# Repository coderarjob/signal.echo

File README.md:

<p align="center">
    
    <br/>
    <br/>

</p>

## About

This is a hardware project based on Atmega8A microcontroller. This project came about from a
personal need for a demo board to test my new oscilloscope. I plan to create a complete PCB
along with firmware in this repo.

**Caution**: The `master` branch contains changes for the upcoming version and may not always be
stable. If you wish to manufacture, use the latest `release/version_x.x` branch or one of the
[released](https://github.com/coderarjob/signal.echo/releases) versions.

See [LICENCE](./LICENSE) for terms under which this project is released and developed.

### Screenshots

##### 1. Serial RS232 (TTL Level) decoding test

##### 2. Serial I2C decoding test

##### 3. Positive & negative Runt detection pulse

##### 4. Burst pulses (long delay)

##### 5. Two burst (time coorolated) pulses

##### 6. Sine wave

##### 7. Amplitude Modulation wave

##### 8. Triangle wave

##### 9. Sawtooth wave

### Goals

- [X] Firmware: RS232 sample output (positive)
- [X] Firmware: I2C sample output
- [X] Firmware: Runt pulse (+ve & -ve runt pulses)
- [X] Firmware: Sine wave pattern
- [X] Firmware: Amplitude Modulation wave pattern
- [X] Firmware: Triangle wave pattern
- [X] Firmware: Sawtooth wave pattern
- [X] Firmware: Burst data in two lines
- [X] Firmware: Separate arch independent codes
- [X] Unittests: Add unittests for utils
- [X] Unittests: Add unittests for existing tests
- [X] Manufacturing: Build the PCB board

## Building prerequisites

1. Requires Linux environment for building.
2. GNU Make
3. avr-gcc
4. avr-libc

### Firmware

Build the firmware using the following command. Firmware binary is the `./out/firmware.hex` file.

```bash
BUILD_DIR=out make
```

To program using avrdude we run the following command.

```bash
make program
```

When programming a new microcontroller, we also need to program the required fuse bits. This can be
using the following command

```bash
make program_fuses
```

### Unittests

We can build every unittests and run them using the `run` target.

```bash
BUILD=ut BUILD_DIR=out/ut make run
```

### Tools

Some tools which are used exclusively in this project are/will be put into the `tools` folder. Each
may have different prerequisites and build procedures. For information see `Readme.md` of each
tool.

# Feedback

Open a GitHub issue or drop a email at arjobmukherjee@gmail.com. I would love to hear your
suggestions and feedbacks.

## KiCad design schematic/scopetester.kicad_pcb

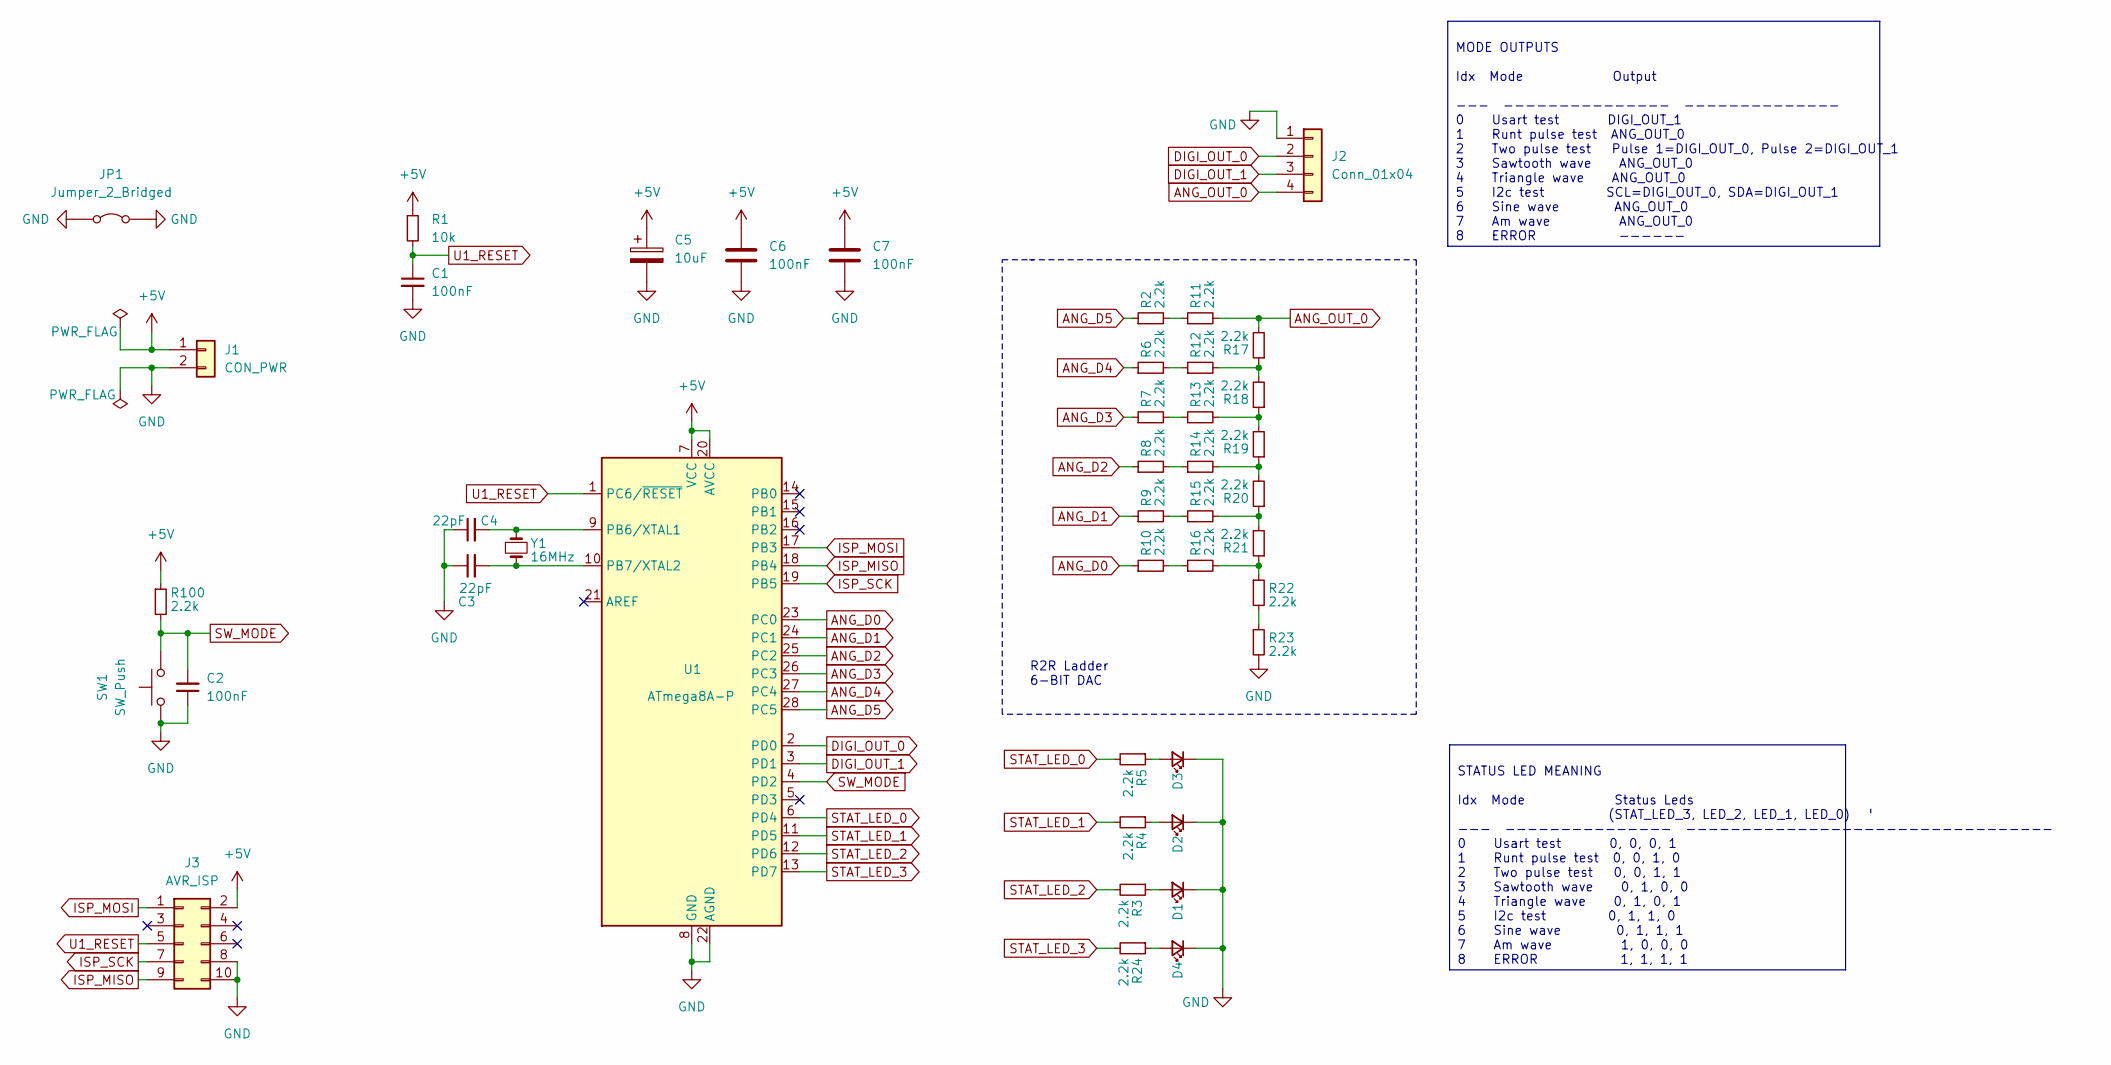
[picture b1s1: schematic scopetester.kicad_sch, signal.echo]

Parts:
C1, C2, C6, C7: 100nF; C_Disc_D3.0mm_W1.6mm_P2.50mm
C3, C4: 22pF; C_Disc_D3.0mm_W1.6mm_P2.50mm
C5: 10uF; CP_Radial_D5.0mm_P2.50mm
D1, D2, D3, D4: LED_Small; LED_D3.0mm
J1: CON_PWR; PinHeader_1x02_P2.54mm_Vertical
J2: Conn_01x04; PinHeader_1x04_P2.54mm_Vertical
J3: AVR_ISP; PinHeader_2x05_P2.54mm_Vertical
JP1: Jumper_2_Bridged; R_Axial_DIN0207_L6.3mm_D2.5mm_P7.62mm_Horizontal
R1: 10k; R_Axial_DIN0207_L6.3mm_D2.5mm_P7.62mm_Horizontal
R2, R3, R4, R5, R6, R7, R8, R9, R10, R11, R12, R13, R14, R15, R16, R17, R18, R19, R20, R21, R22, R23, R24: 2.2k; R_Axial_DIN0207_L6.3mm_D2.5mm_P7.62mm_Horizontal
R100: 2.2k; R_Axial_DIN0411_L9.9mm_D3.6mm_P5.08mm_Vertical
SW1: SW_Push; SW_PUSH_6mm_H4.3mm
U1: ATmega8A-P; DIP-28_W7.62mm
Y1: 16MHz; Crystal_HC49-4H_Vertical

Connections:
+5V: C5.1, C6.1, C7.1, J1.1, J3.2, R1.1, R100.1, U1.7 (VCC), U1.20 (AVCC)
ANG_D0: R10.1, U1.23 (PC0)
ANG_D1: R9.1, U1.24 (PC1)
ANG_D2: R8.1, U1.25 (PC2)
ANG_D3: R7.1, U1.26 (PC3)
ANG_D4: R6.1, U1.27 (PC4)
ANG_D5: R2.1, U1.28 (PC5)
ANG_OUT_0: J2.4, R11.2, R17.2
DIGI_OUT_0: J2.2, U1.2 (PD0)
DIGI_OUT_1: J2.3, U1.3 (PD1)
GND: C1.2, C2.1, C3.1, C4.1, C5.2, C6.2, C7.2, D1.1 (K), D2.1 (K), D3.1 (K), D4.1 (K), J1.2, J2.1, J3.8, J3.10, JP1.1 (A), JP1.2 (B), R23.2, SW1.1, U1.8 (GND), U1.22 (AGND)
ISP_MISO: J3.9, U1.18 (PB4)
ISP_MOSI: J3.1, U1.17 (PB3)
ISP_SCK: J3.7, U1.19 (PB5)
unnamed: D1.2 (A), R3.1
unnamed: D2.2 (A), R4.1
unnamed: D3.2 (A), R5.1
unnamed: D4.2 (A), R24.1
unnamed: R10.2, R16.1
unnamed: R2.2, R11.1
unnamed: R6.2, R12.1
unnamed: R12.2, R17.1, R18.2
unnamed: R7.2, R13.1
unnamed: R13.2, R18.1, R19.2
unnamed: R8.2, R14.1
unnamed: R14.2, R19.1, R20.2
unnamed: R9.2, R15.1
unnamed: R15.2, R20.1, R21.2
unnamed: R16.2, R21.1, R22.1
unnamed: R22.2, R23.1
unnamed: C4.2, U1.9 (PB6/XTAL1), Y1.1
unnamed: C3.2, U1.10 (PB7/XTAL2), Y1.2
STAT_LED_0: R5.2, U1.6 (PD4)
STAT_LED_1: R4.2, U1.11 (PD5)
STAT_LED_2: R3.2, U1.12 (PD6)
STAT_LED_3: R24.2, U1.13 (PD7)
SW_MODE: C2.2, R100.2, SW1.2, U1.4 (PD2)
U1_RESET: C1.1, J3.5, R1.2, U1.1 (PC6/~RESET)

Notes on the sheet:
R2R Ladder 6-BIT DAC
MODE OUTPUTS Idx Mode Output --- --------------- -------------- 0 Usart test DIGI_OUT_1 1 Runt pulse test ANG_OUT_0 2 Two pulse test Pulse 1=DIGI_OUT_0, Pulse 2=DIGI_OUT_1 3 Sawtooth wave ANG_OUT_0 4 Triangle wave ANG_OUT_0 5 I2c test SCL=DIGI_OUT_0, SDA=DIGI_OUT_1 6 Sine wave ANG_OUT_0 7 Am wave A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
STATUS LED MEANING Idx Mode Status Leds (STAT_LED_3, LED_2, LED_1, LED_0) --- --------------- --------------------------------- 0 Usart test 0, 0, 0, 1 1 Runt pulse test 0, 0, 1, 0 2 Two pulse test 0, 0, 1, 1 3 Sawtooth wave 0, 1, 0, 0 4 Triangle wave 0, 1, 0, 1 5 I2c test 0, 1, 1, 0 6 Sine wave 0,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

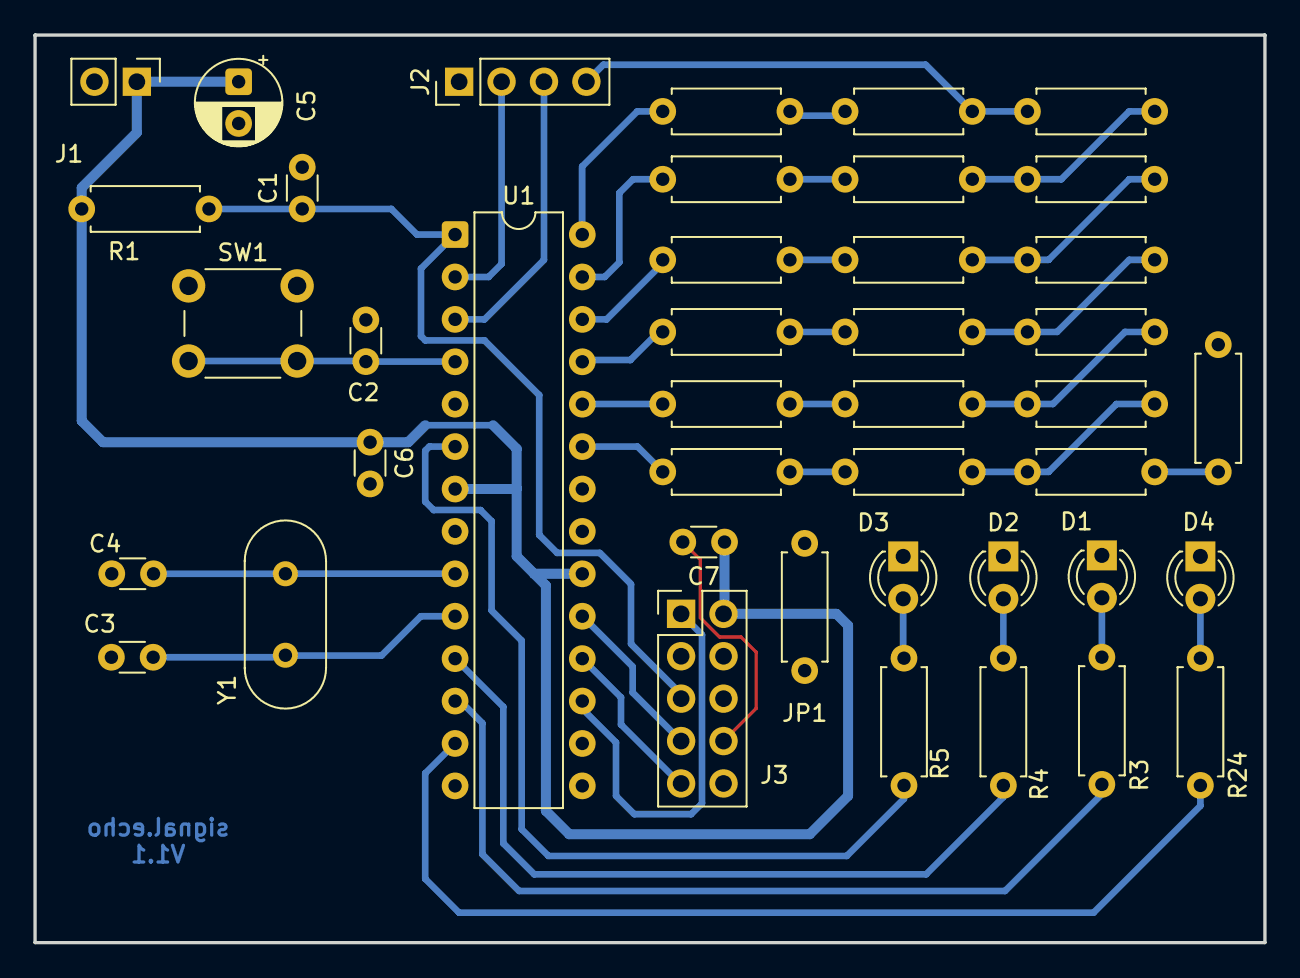
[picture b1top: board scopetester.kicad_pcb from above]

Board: 2 copper layers, 73.7 x 54.4 mm, 42 parts (0 on the bottom side), 38 nets.

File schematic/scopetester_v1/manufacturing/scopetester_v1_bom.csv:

"Id";"Designator";"Footprint";"Quantity";"Designation";"Supplier and ref";
1;"J3";"PinHeader_2x05_P2.54mm_Vertical";1;"AVR_ISP";;;
2;"U1";"DIP-28_W7.62mm";1;"ATmega8A-P";;;
3;"C6,C7,C1,C2";"C_Disc_D3.0mm_W1.6mm_P2.50mm";4;"100nF";;;
4;"JP1";"R_Axial_DIN0207_L6.3mm_D2.5mm_P7.62mm_Horizontal";1;"Jumper_2_Bridged";;;
5;"R8,R5,R9,R23,R12,R21,R18,R3,R6,R19,R16,R20,R7,R11,R14,R13,R15,R24,R4,R22,R2,R10,R17";"R_Axial_DIN0207_L6.3mm_D2.5mm_P7.62mm_Horizontal";23;"2.2k";;;
6;"D1,D3,D4,D2";"LED_D3.0mm";4;"LED_Small";;;
7;"Y1";"Crystal_HC49-4H_Vertical";1;"16MHz";;;
8;"SW1";"SW_PUSH_6mm_H4.3mm";1;"SW_Push";;;
9;"J2";"PinHeader_1x04_P2.54mm_Vertical";1;"Conn_01x04";;;
10;"C5";"CP_Radial_D5.0mm_P2.50mm";1;"1uF";;;
11;"R1";"R_Axial_DIN0207_L6.3mm_D2.5mm_P7.62mm_Horizontal";1;"10k";;;
12;"C4,C3";"C_Disc_D3.0mm_W1.6mm_P2.50mm";2;"22pF";;;
13;"J1";"PinHeader_1x02_P2.54mm_Vertical";1;"CON_PWR";;;

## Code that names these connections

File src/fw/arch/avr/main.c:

#include <avr/io.h>
#include <stdint.h>
#include <util/delay_basic.h>
#include <avr/interrupt.h>
#include <stdbool.h>
#include <main.h>

#define SWITCH_PIN_NO PD2
#define SWITCH_PORT   PORTD
#define SWITCH_PIN    PIND
#define SWITCH_DDR    DDRD

#define STATUS_PIN_NO PB1
#define STATUS_PORT   PORTB
#define STATUS_PIN    PINB
#define STATUS_DDR    DDRB

#define RUNT_OUTPUT_PORT   PORTC
#define RUNT_OUTPUT_DDR    DDRC

#define HOLDOFF_OUTPUT_PIN_NO PD1
#define HOLDOFF_OUTPUT_PORT   PORTD
#define HOLDOFF_OUTPUT_DDR    DDRD

typedef enum TestModes {
    UNKNOWN_TEST,
    USART_TEST,
    HOLDOFF_TEST,
    RUNT_PULSE,
    TEST_COUNT
} TestModes;

static volatile TestModes mode;
static volatile bool mode_isDirty;

static void usart_test();
static void holdoff_test();
static void runt_pulse_test();

ISR (INT0_vect)
{
    if (++mode >= TEST_COUNT) {
        mode = USART_TEST;
    }

    mode_isDirty = true;

    BIT_SET (STATUS_PORT, STATUS_PIN_NO);

    // Wait for the pin to be high
    while (!IS_BIT_SET (SWITCH_PIN, SWITCH_PIN_NO))
        ;

    BIT_CLEAR (STATUS_PORT, STATUS_PIN_NO);
}

void setup_io()
{
    // Make the Interrupt 0 pin as the input
    MAKE_PIN_INPUT_PULLUP (SWITCH_DDR, SWITCH_PORT, SWITCH_PIN_NO);

    // Enable interrupt
#if SWITCH_PIN_NO != PD2
    #error "Wrong switch pin set"
#endif

    BIT_CLEAR_MASK (MCUCR, (1 << ISC01 | 1 << ISC00)); // Trigger at Low level
    BIT_SET_MASK (GICR, (1 << INT0));                  // Enable the interrupt

    // Status port
    MAKE_PIN_OUTPUT (STATUS_DDR, STATUS_PIN_NO);
    BIT_CLEAR (STATUS_PORT, STATUS_PIN_NO);

    sei();
}

__attribute__ ((noreturn)) void main (void)
{
    mode         = USART_TEST;
    mode_isDirty = true;

    setup_io();

    while (1) {
        mode_isDirty = false;
        switch (mode) {
        case USART_TEST:
            usart_test();
            break;
        case HOLDOFF_TEST:
            holdoff_test();
            break;
        case RUNT_PULSE:
            runt_pulse_test();
            break;
        default:
            BIT_SET (STATUS_PORT, STATUS_PIN_NO);
            break;
        }
    }
}

static void runt_pulse_test()
{
    RUNT_OUTPUT_DDR = 0xFF; // Make every pin as output
    uint32_t runt_freq = 1000; // 1 rust pulse every 100 normal pulses

    for (; !mode_isDirty;) {
        if (--runt_freq == 0) {
            runt_freq = 1000;
            RUNT_OUTPUT_PORT = (0x7 << 1); // Make PC1:PC4 as high
            _delay_loop_2 (255);
            RUNT_OUTPUT_PORT = (0);
            _delay_loop_2 (255);
        } else {
            RUNT_OUTPUT_PORT = (0xF<<1); // Make PC1:PC4 as high
            _delay_loop_2 (512);
        }
        RUNT_OUTPUT_PORT = 0x0; // Make all pins low
        _delay_loop_2 (512);
    }

    RUNT_OUTPUT_PORT = 0x0; // Make all pins low
}

static void holdoff_test()
{
    MAKE_PIN_OUTPUT (HOLDOFF_OUTPUT_DDR, HOLDOFF_OUTPUT_PIN_NO);

    for (; !mode_isDirty;) {
        for (int i = 0; i < 20; i++) {
            BIT_SET (HOLDOFF_OUTPUT_PORT, HOLDOFF_OUTPUT_PIN_NO);
            _delay_loop_1 (255);
            BIT_CLEAR (HOLDOFF_OUTPUT_PORT, HOLDOFF_OUTPUT_PIN_NO);
            _delay_loop_1 (255);
        }
        _delay_loop_2 (65535);
    }
}

void usart_test()
{
    usart_on();
    for (char c = 'A'; !mode_isDirty; c + 1 > 'Z' ? c = 'A' : c++) {
        _delay_loop_2 (65535);
        usart_send_string ("Arjob");
        usart_send_char (c);
    }
    usart_off();
}

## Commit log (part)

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2025-05-30 Compiler definitions moved to toolchain file
2025-05-30 Added checks to validate various build variables
2025-05-30 Make rules added to program micro using avrdude
2025-06-04 Targets are build in the respective build.mk
    This make more sense and keeps the outer Makefile less polluted with
    details.
2025-06-04 An example unittest and supporting build added
2025-06-04 New 'run' target to build & run all unittests
2025-06-05 Arch dependent parts separated from independent ones
2025-06-05 Added clang-format for the project
2025-06-05 Static inline small HW functions
    This does reduce the size of the output binary a little bit, but this
    change is more of a placeholder of later functions of the same nature.
2025-06-05 Added utils unittest
2025-06-05 Minor renaming & refactoring in utils.h
2025-06-05 Fix: HIGH8 unittest failure
    To find the highest byte (most significant byte) we must know total
    number of bits. Previously 16 bits was assumed, giving a value higher
    than 65535 thus produced wrong result.
    We now have two separate macros for 16 bit and 32 bit words.
2025-06-05 Unittest for various the main features
    Tests added for:
    * usart_test
    * holdoff_test
    * runt_pulse_test
2025-06-05 Fix: Usart sending wrong first character
2025-06-05 Readme update
2025-06-05 Simplification of mode_is_dirty handler
    Also includes:
    * Minor change to usart_test_normal to check if output char is
    incremented per iteration.
2025-06-05 Fix: Firmware Hex file not passed to Programmer
2025-06-05 Now produces both +ve & -ve runt pulses
    Also include:
    * Associated Unittest update
2025-06-05 Updated yukti.h to latest
    Commit: 6ee1a12
2025-06-05 Add command to build/run unittests in Readme
    Other minor changes to Readme.
2025-06-05 reset_all_mocks() to reset all mock functions
2025-06-06 Fix: Wrong height of Negative runt pulse
    DAC pins are PC1-PC4. PC0 is unused. However low level bits was written
    to PC0-PC2 which caused the problem.
2025-06-06 Readme update with screenshots
2025-06-06 Fix: Readme image alignment issues
2025-06-07 Updated yukti.h to latest
    Commit: 5749a16
    Also includes:
    * Changes to feature_test to use new features in Yukti
2025-06-08 New Two Pulses Test for osc trigger testing
2025-06-08 Readme update with project logo
2025-06-08 Cleanup: Remove hw.h file
    It contained function declarations of functions whose implementations
    are arch dependent, but use is arch independent. By convention such
    functions need no be in a special file. Placing them in main.h file
    would serve the purpose.
2025-06-08 New unittest for two_pulses_test
2025-06-09 Remove separate holdoff test
    Burst mode test can be used for holdoff testing.
2025-06-09 Fix: Current Mode is unknwon state at startup
2025-06-09 Resize burst mode screenshot
    Also includes:
    * Remove holdoff test screenshots
2025-06-10 Replace logo.svg with logo.png
    Vector graphics requires all the referenced font to be present in the
    system to look the same. This is not a guarantee.
    Also includes:
    * Some spelling corrections in Readme
2025-06-10 Burst mode pulses are not narrow & more in number
    There is also a difference in width for the two pulses.
2025-06-15 Analog pins changed. Now starts from PC0 not PC1
2025-06-15 Now only output pins are made output in hw_init()
2025-06-15 DAC is now 6 bits wide instead of 4
2025-06-15 DIGITAL_OUTPUT_PIN_NO0 is now PD0 not PD1
    This aligns with schematic and common sense!
2025-06-15 3 LED's now show current mode
2025-06-15 Fix: Switch debouncing
2025-06-17 Minor updates, makes DAC clear & change of title
2025-06-20 AVR HAL Initial commit
2025-06-20 Using HAL to simplify firmware source code (UT failing)
    * HAL is the only arch dependent code. Tests and even HW initialization
    are done in arch/hw schematic independent way.
    * HW has its versions & is defined in include/hw/<ver>/hwspec.h file.
2025-06-21 hwspec.h should only reference arch independent types
    Otherwise it becomes difficult to unittest with a arch independent
    mocked hal.
    Fixed for AVR_HAL_INTERRUPTS_EXT_INTERRUPT0 which was referenced from
    hwspec.h.
2025-06-21 hal.h file is now included by relative path
    This is done to mock hal.h easily from the build script side.
2025-06-21 Update yukti.h to latest
    Commit: 356c003
    FIX: Build error when mocks & tests are placed separately
    Now the header file is structured to make this separation clear. Things
    that only need to for YT_DEFINE_FUNC*, YT_DECLARE_FUNC* & YT_RESET_MOCK
    macros are defined separate from the ones which are test implementation
    related. The later macros, function etc are now under
2025-06-21 Fix: two_pulses_test used wrong mask for output gpio
2025-06-21 Fix: Baud counter calculation fixed in AVR HAL
2025-06-22 Triangle wave generation added
2025-06-22 Remove zero delays for sawtooth & triangle waves
2025-06-22 Update readme with new Screenshots
2025-06-22 Updated screenshots after last commit
2025-06-22 Added few more informative Screenshots of tests
2025-06-23 Refactoring not include nops for unittests builds
2025-06-25 I2C test added
    Bit banging i2c implementation was added. It sends I2C packet with
    address & data bytes.
    Also includes:
    * Screenshot & Readme update
2025-06-26 Modes updated in schematic & initial PCB layout
2025-06-28 Update yukti.h to latest
    Adds support for parameterised testing
    Commit ID: 4cb359b
    Minor change to make test index & number explicit
2025-06-28 Modify utils test to use parameterised testing
2025-06-28 Updated yukti.h to latest
    Fixes build failure after last commit. New YT_ARG_SUB_ARRAY macro.
    Commit ID: 2dbf4aa
    Added a more complex parameterised test example.
2025-06-28 Status LED out derived from current TestMode
    Previously they were 1:1 mapped.
2025-06-28 Make FW main.c testable, unittest added for it
2025-06-29 Fix: YUKTI_TEST_IMPLEMENTATION not working
    This happens if yukti.h is included from from another header - (for
    example from a mock header) before the YUKTI_TEST_IMPLEMENTATION is
    defined in the test source file.
    One solution is to define YUKTI_TEST_IMPLEMENTATION and include yukti.h
    in the first line in test source.
2025-06-29 Moved DAC_* macros to hwspec.h as they are HW spec related
2025-06-29 Rename TestModes items as TEST_MODE_*
2025-07-02 There are now 4 status LEDs instead of 3
2025-07-02 Fix: Sine wave shape
2025-07-02 Update Readme with Sine wave screenshots
2025-07-04 Sine wave data is put on the .data section explicitly
    This produces same assembly expect for one LDI instruction within the
    loop, related to the 'for' loop in sine_test function. This extra
    instruction causes little dip in the output freq, but is otherwise same.
2025-07-04 Added Timer0 interrupt to avr/hal
2025-07-04 Screenshot update
2025-07-05 Replaced Vcc with +5V in schematic
2025-07-06 Fix: More proper footprints instead of guessing
2025-07-08 Multiple fixes to PCB layout (not final)
2025-07-09 More compact PCB layout
2025-07-09 Finalized PCB layout (edition 1)
    The DRC error of 'mission connection between items' was solved using a
    phony track on the front side. This is just to satisfy KiCad because it
    does not seem to understand that jumper is actually bridged.
2025-07-12 SineX on X and Amplitude Modulation waveform added
    Also includes:
    Corresponding changes to unittests
2025-07-17 Now using 16MHz clock instead of 12MHz
    This increases the waveform frequencies by 33.3%.
2025-07-17 Rename macro MPU_ARCH -> ARCH
    This aligns both Makefile variable & C macro names used to identify MMU
    architecture.
2025-07-17 HAL_BAUD_COUNTER now takes CPU freq as input
2025-07-17 hal_impl_panic is fully mocked for unittest
    Also includes:
    * Fixes compiler warning during unittest 'noreturn function returning'.
2025-07-20 Update yukti.h to latest
    Commit ID: 5f57ade
    Example added for YT_MUST_CALL_* expectations
    Also includes:
    * More comments added to tests
2025-07-25 Upgrade yukti.h to latest
    Commit ID: b96caf0
    Updated to get the following changes:
    * Elapsed time for each is test is displayed
    * New simplified test outputs
2025-08-02 Tool to produce values for our DAC
2025-08-02 Provision to not use Zig's LLVM backend
    Setting `LLVM=0` before `make` will use Zig compiler's native backend
    (which is faster) instead of the default LLVM.
2025-08-02 Using .init to initialize GeneralPurposeAllocator
    As per the deprecation note in the source code and examples in the
    zig release notice.
2025-08-08 Fix: Waves not reaching max and zero values
    It was caused by floor operation in transform_waveform function.
2025-08-10 Update kicad Project to Kicad-9
2025-08-12 bulid.zig replaces Makefile
    It is only required to provide the zig compiler the 'root' file, and
    from that it determines what other files it needs to compile. This is
    difficult to do from within a Makefile.
2025-08-12 Linear interpolation added to smooth to a degree
    Also includes:
    * Option added to enable interpolation & set frequency scaling from
    command arguments.
2025-08-12 Added waveforms data
2025-08-12 Make argument parsing more cleaner
2025-08-13 Move wave generation code into a new file
2025-08-13 Removed Sinx/x wave with much larger AM wave data
    Removed because I think a more dense AM wave will be more useful than a
    sine(x)/x wave for testing purposes.
2025-08-13 Fix: Unittest build failure after d8fdfe4
2025-08-15 New implementation for wave generation
    See explanation in `docs/wave_gen.md`
2025-08-15 AM wave generated using new algo
    6000 points, 4x freq scaling gives a nice envelope but at the cost of
    individual wave look.
    Also includes:
    * Waveform data for 6000 points, 4x and 2x frequency scaling AM.
2025-08-15 Minor changes to comments in schematic
2025-08-15 Unittest for Sine and AM wave dump function
2025-08-15 Add GitHub workflow to build & run unittests
2025-08-15 GW: Fix: avr-gcc not found
2025-08-15 GW: Fix: Build failure - no rule to make target 'run'
2025-08-15 New logo for the project added
2025-08-15 Added GBR and BOM files
2025-08-16 Fix: Spelling mistake in the GitHub logo
2025-08-18 Fix: Minor spelling mistakes in usage
2025-08-18 Fix: DacValues: Test build failure
2025-08-25 Source now compiles with Zig 0.15.1
2025-08-26 PCB changes to make layout less dense
2025-08-26 Minor changes, project name & version update
2025-09-03 Added a note that project is still is development
2025-09-05 Remove 'In Development' message after the latest PCB working
2025-09-06 hw: Added info about outputs depending on modes
    Also includes:
    * Title update in the schematic. ScopeTester -> signal.echo.
    * GitHub repo link added to schematic description.
2025-09-07 Remove HW_VER option from build and FW source
    Because `master` branch will only support one hardware - the one in
    development. Each released version will be in separate branch thus is
    not affected by changes in the master branch.
2025-09-07 Remove '_v1' from schematic files names
    See previous commit for reason.
2025-09-07 Release spec for Version 1.0
2025-09-07 Readme update which links to released page
2025-09-07 Update project name in Licence file
2025-09-07 Minor update to caution message in Readme
2025-09-14 Fix: Wrongly generated AM wave
    The AM wave gen calculation was wrong resulting is wrong frequency
    components, which can be seen in the FFT and also just at looking at the
    shape of the wave.
    Multiple changes were done surrounding this fix.
    * tools/DacValues
    * Fix: AM wave gen calculation
2025-09-14 Update RELEASE document after 401d1b0
2025-09-14 tools: Fix: Incorrect statements & spelling mistakes
2025-09-18 Fix: Spelling mistakes
2026-04-06 Adds new burst pulses test
    Also includes:
    * Unittest for the same
2026-04-06 Fix: burst_pulses_test was actually never called
2026-04-06 Fix: Mode change did not work in burst pulses test
    Happened because mode change was not checked within the loop within
    long_delay function
2026-04-07 Lower the delay between bursts to something sane
2026-04-07 Test updated to validate burst_pulses_test call from main
2026-04-07 Schematic updated to show Burst Pulses test output
2026-04-07 Screenshots for burst pulses test added
2026-04-15 Successful compilation with Zig 0.16.0 version
